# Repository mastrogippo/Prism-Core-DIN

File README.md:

## Prism Core boards and accessories

[Writeup and pics here](https://www.mastrogippo.it/2019/09/prism-core-boards/)

cover_pcb: Cover board layout

hv_in3: Base high voltage board for Prism Core

lato1: Left board with relay and HV detection for Prism Core

latoLV: Low voltage side board for Prism Core

top: Tob board with SKW92 module for Prism Core

top_hk2: Top board with HiLink module and RTC for Prism Core

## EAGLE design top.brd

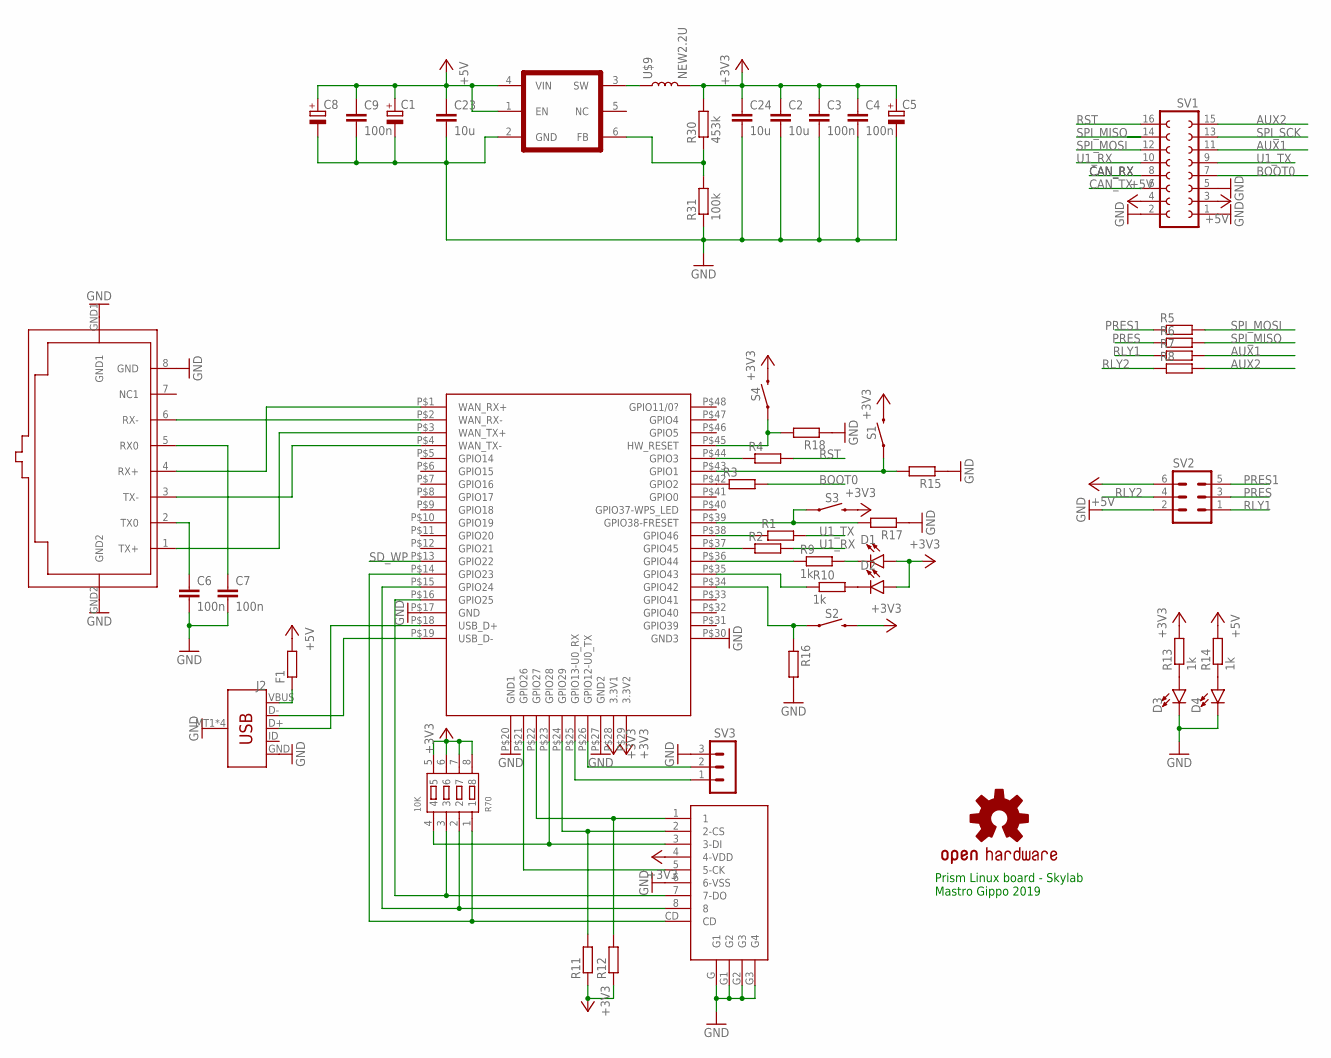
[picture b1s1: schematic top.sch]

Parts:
C1, C5, C8: CPOL-EUB/3528-21R; B/3528-21R
C2, C23, C24: 10u; C0805K
C3, C4, C6, C7, C9: 100n; C0805K
D1, D2: LED3MM; LED_3MM
D3, D4: LED1206; LED-1206
F1: R-EU_R0603; R0603
J2: USB_MICRO-B_SMT; USB-MICROB
R1, R2, R3, R4, R5, R6, R7, R8, R11, R12, R15, R16, R17, R18: R-EU_R0805; R0805
R9, R10, R13, R14: 1k; R0805
R30: 453k; R0805
R31: 100k; R0805
R70: 10K; RA1206-8
S1, S2, S4: MOMENTARY-SWITCH-SPST-SMD-6.0X3.5MM; TACTILE_SWITCH_SMD_6.0X3.5MM
S3: MOMENTARY-SWITCH-SPST-PTH-RIGHT-ANGLE; TACTILE_SWITCH_PTH_RIGHT_ANGLE
SV1: FE08-2
SV2: MA03-2
SV3: MA03-1
U$1: RJ45-TRAFO
U$2: SKW92B; SKW92
U$3: MICRO_SD; MICRO_SD_C
U$4: OSHW-LOGOS; OSHW-LOGO-S
U$8: TLV62658; SOT23-6
U$9: NEW2.2U; INDUCTOR_4X4MM

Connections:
+3V3: C2.1, C3.1, C4.1, C5.+, C24.1, D1.A, D2.A, R11.1, R12.1, R13.2, R30.2, R70.5, R70.6, R70.7, R70.8, S1.2, S2.2, S3.2, S4.2, U$2.P$28 (3.3V1), U$2.P$29 (3.3V2), U$3.4 (4-VDD), U$9.P$2 (2)
+5V: C1.+, C8.+, C9.1, C23.1, F1.2, R14.2, SV1.3, SV1.4, SV2.6, U$8.1 (EN), U$8.4 (VIN)
AUX1: R7.2, SV1.11
AUX2: R8.2, SV1.15
BOOT0: R3.2, SV1.7
CAN_RX: SV1.8
CAN_TX: SV1.6
GND: C1.-, C2.2, C3.2, C4.2, C5.-, C6.2, C7.2, C8.-, C9.2, C23.2, C24.2, D3.C, D4.C, J2.GND, J2.MT1 (SHIELD), J2.MT2 (SHIELD), J2.P$1 (SHIELD), J2.P$2 (SHIELD), R15.1, R16.2, R17.1, R18.1, R31.1, SV1.1, SV1.2, SV1.5, SV2.2, SV3.3, U$1.8 (GND), U$1.GND1, U$1.GND2, U$2.P$17 (GND), U$2.P$20 (GND1), U$2.P$27 (GND2), U$2.P$30 (GND3), U$3.6 (6-VSS), U$3.G (G1), U$3.G1 (G2), U$3.G2 (G3), U$3.G3 (G4), U$8.2 (GND)
unnamed: U$1.6 (RX-), U$2.P$2 (WAN_RX-)
unnamed: U$1.4 (RX+), U$2.P$1 (WAN_RX+)
unnamed: U$1.1 (TX+), U$2.P$3 (WAN_TX+)
unnamed: U$1.3 (TX-), U$2.P$4 (WAN_TX-)
unnamed: R11.2, U$2.P$24 (GPIO29), U$3.2 (2-CS)
unnamed: R70.4, U$2.P$23 (GPIO28), U$3.3 (3-DI)
unnamed: R12.2, U$2.P$22 (GPIO27), U$3.1
unnamed: U$2.P$21 (GPIO26), U$3.5 (5-CK)
unnamed: R70.3, U$2.P$16 (GPIO25), U$3.7 (7-DO)
unnamed: R70.2, U$2.P$15 (GPIO24), U$3.8
unnamed: R70.1, U$2.P$14 (GPIO23), U$3.CD
unnamed: R1.1, U$2.P$38 (GPIO46)
unnamed: R2.1, U$2.P$37 (GPIO45)
unnamed: R3.1, U$2.P$42 (GPIO2)
unnamed: R4.1, U$2.P$44 (GPIO3)
unnamed: D1.K (C), R9.2
unnamed: SV3.2, U$2.P$26 (GPIO12-U0_TX)
unnamed: SV3.1, U$2.P$25 (GPIO13-U0_RX)
unnamed: D2.K (C), R10.2
unnamed: R9.1, U$2.P$36 (GPIO44)
unnamed: R10.1, U$2.P$35 (GPIO43)
unnamed: D3.A, R13.1
unnamed: D4.A, R14.1
unnamed: R15.2, S1.1, U$2.P$43 (GPIO1)
unnamed: R16.1, S2.1, U$2.P$34 (GPIO42)
unnamed: R17.2, S3.1, U$2.P$39 (GPIO38-FRESET)
unnamed: R18.2, S4.1, U$2.P$45 (HW_RESET)
unnamed: C7.1, U$1.5 (RX0)
unnamed: C6.1, U$1.2 (TX0)
unnamed: J2.D+, U$2.P$18 (USB_D+)
unnamed: J2.D-, U$2.P$19 (USB_D-)
unnamed: F1.1, J2.VBUS
unnamed: U$8.3 (SW), U$9.P$1 (1)
unnamed: R30.1, R31.2, U$8.6 (FB)
PRES: R6.1, SV2.3
PRES1: R5.1, SV2.5
RLY1: R7.1, SV2.1
RLY2: R8.1, SV2.4
RST: R4.2, SV1.16
SD_WP: U$2.P$13 (GPIO22)
SPI_MISO: R6.2, SV1.14
SPI_MOSI: R5.2, SV1.12
SPI_SCK: SV1.13
U1_RX: R2.2, SV1.10
U1_TX: R1.2, SV1.9

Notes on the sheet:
Prism Linux board - Skylab Mastro Gippo 2019

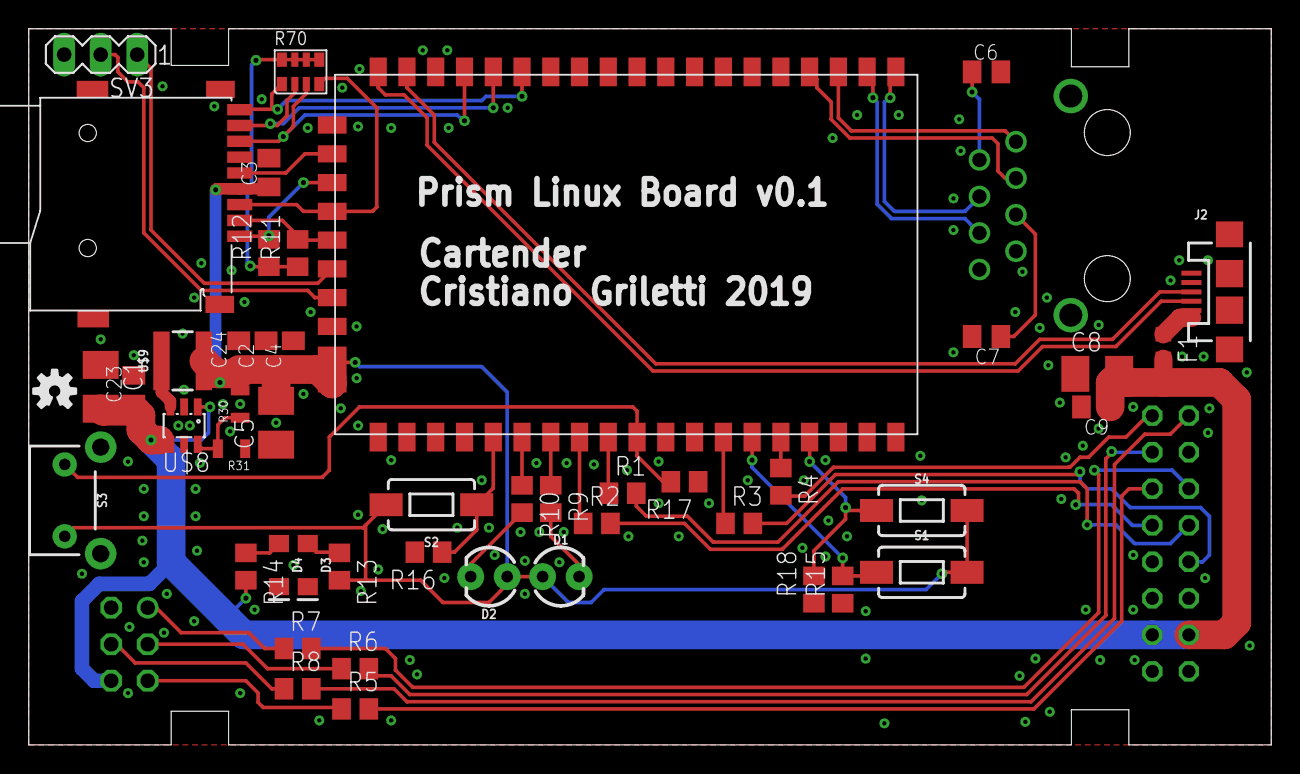
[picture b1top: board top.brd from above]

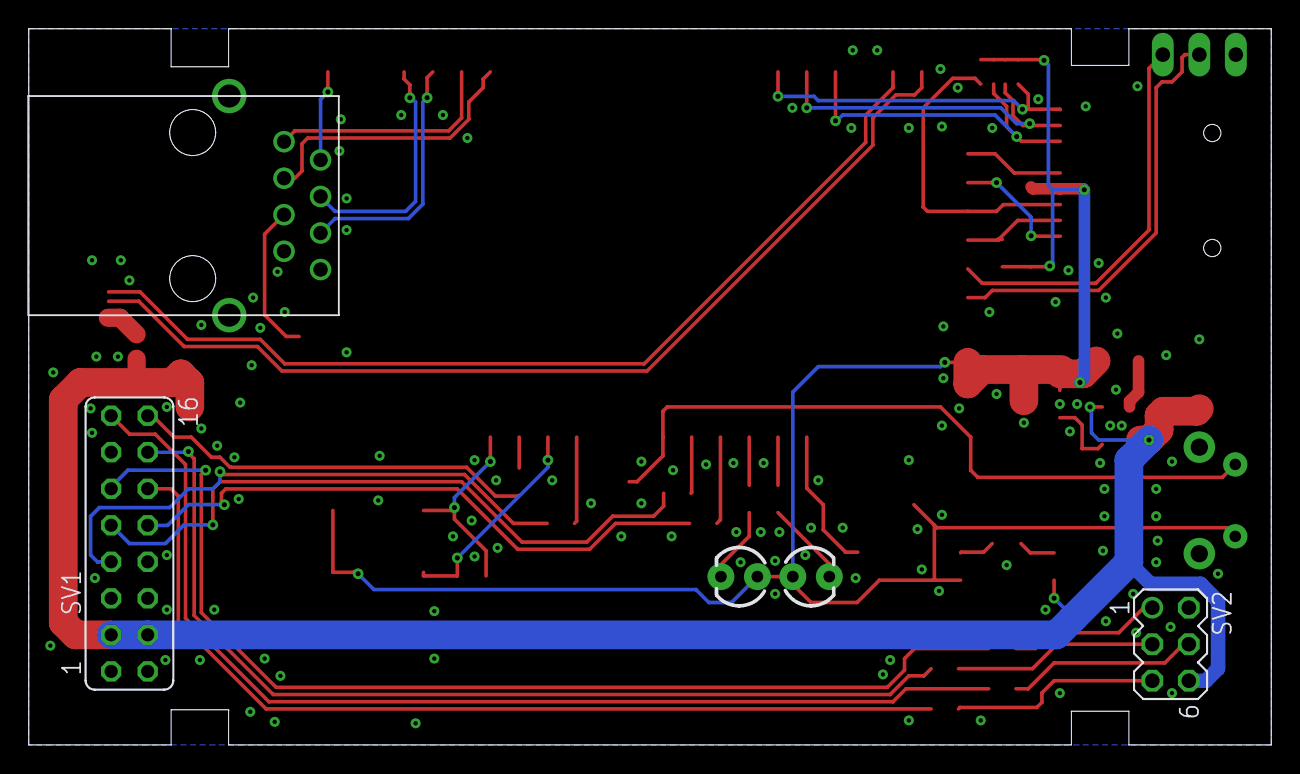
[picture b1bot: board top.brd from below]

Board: 2 copper layers, 86.4 x 49.8 mm, 51 parts (3 on the bottom side), 49 nets.

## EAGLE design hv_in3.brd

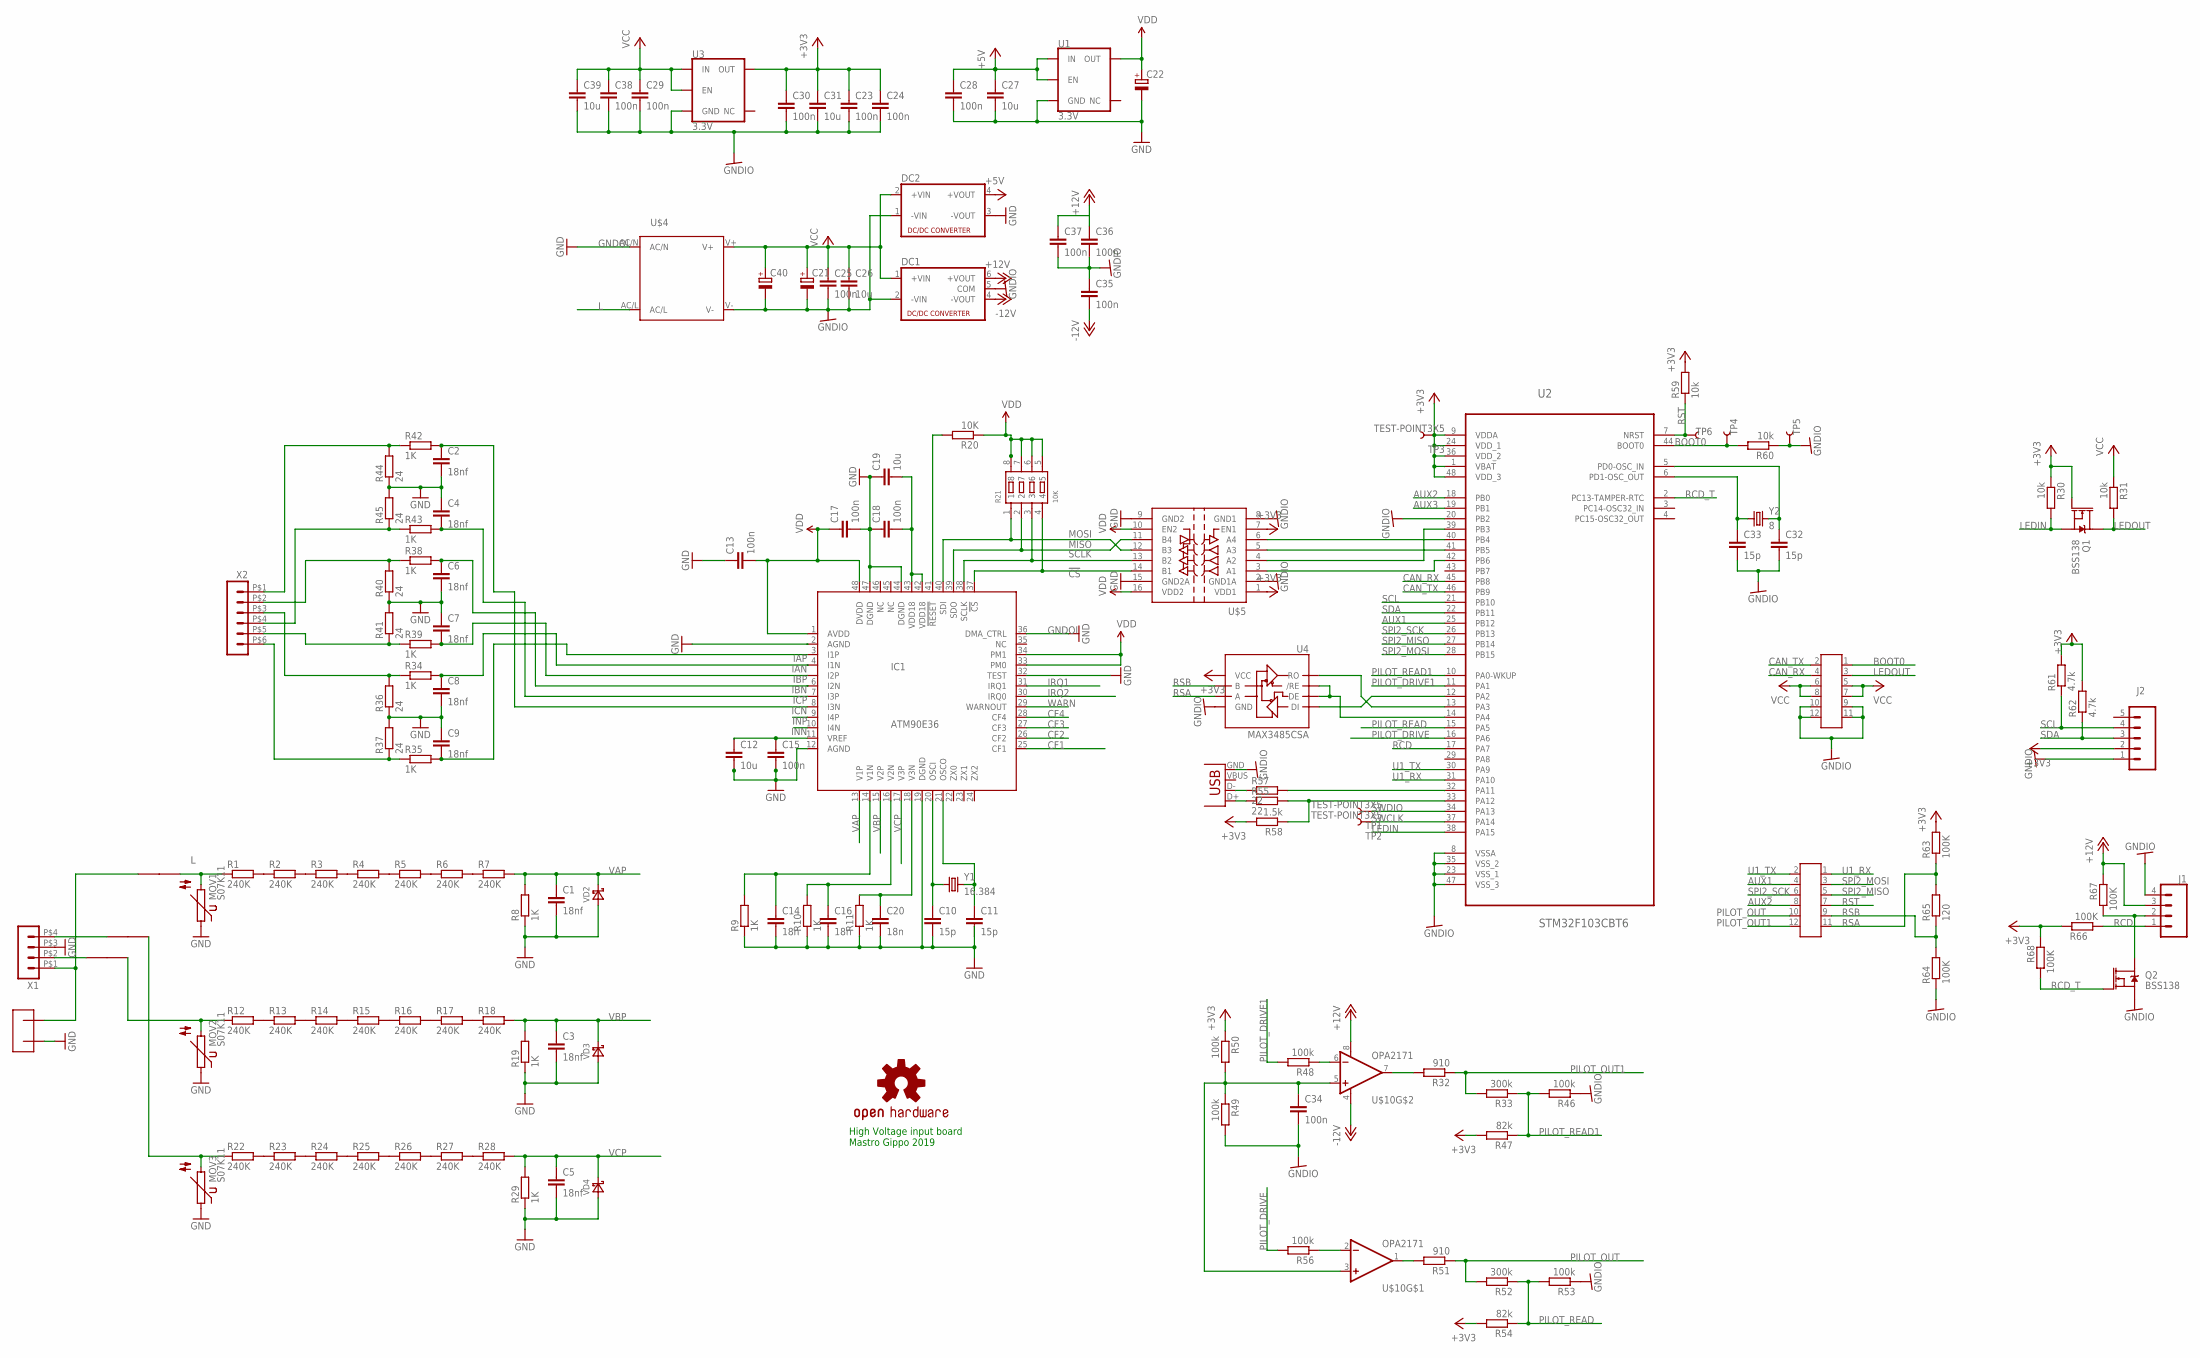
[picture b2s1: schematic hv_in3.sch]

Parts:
C1, C2, C3, C4, C5, C6, C7, C8, C9: 18nf; C0805K
C10, C11, C32, C33: 15p; C0805K
C12, C19, C26, C27, C31, C39: 10u; C0805K
C13, C15, C17, C18, C23, C24, C25, C28, C29, C30, C34, C35, C36, C37, C38: 100n; C0805K
C14, C16, C20: 18n; C0805K
C21, C22: CPOL-EU153CLV-0505; 153CLV-0505
C40: CPOL-EUB/3528-21R; B/3528-21R
DC1: NMA
DC2: NME
IC1: ATM90E36; TQFP48
J1: CONN_04SMD2; 1X04_1MM_RA
J2: CONN_05SMD2; 1X05_1MM_RA
MOV1, MOV2, MOV3: S07K11
Q1, Q2: BSS138; SOT23-3
R1, R2, R3, R4, R5, R6, R7, R12, R13, R14, R15, R16, R17, R18, R22, R23, R24, R25, R26, R27, R28: 240K; R0805
R8, R9, R10, R11, R19, R29, R34, R35, R38, R39, R42, R43: 1K; R0805
R20: 10K; R0805
R21: 10K; RA1206-8
R30, R31, R59, R60: 10k; R0805
R32, R51: 910; R1206
R33, R52: 300k; R0805
R36, R37, R40, R41, R44, R45: 24; R0805
R46, R48, R49, R50, R53, R56: 100k; R0805
R47, R54: 82k; R0805
R55, R57: 22; R0805
R58: 1.5k; R0805
R61, R62: 4.7k; R0805
R63, R64, R66, R67, R68: 100K; R0805
R65: 120; R0805
TP1, TP2, TP3, TP4, TP5, TP6: TEST-POINT3X5; PAD.03X.05
U1, U3: 3.3V; SOT23-5
U2: STM32F103CBT6; QFP50P900X900X160-48N
U4: MAX3485CSA; SO08
U$1, U$2, U$3: FUSE_2410; 2410_F
U$4: IRM_15/20IRM_15/20; IRM_15/20
U$5: SI8441IS1; SO16
U$6: ISOLATED_2P; STRIP_NOMIDDLE
U$7, U$8: CLP-106-02-F-D-P; CLP-106-02-X-D
U$9: OSHW-LOGOS; OSHW-LOGO-S
U$10: OPA2171; SO08
VD2, VD3, VD4: DIODE-SCHOTTKY-SOD523; SOD523
X1: HEADER_POS4_43045-0401; 43045-0400
X2: HEADER_POS6_43045-0600; 43045-0600
X3: USB-MICROB
Y1: 16.384; CRYSTAL-SMD-3.2X2.5MM
Y2: 8; CRYSTAL-SMD-3.2X2.5MM

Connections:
!CS: IC1.37 (!CS), R21.4, U$5.14 (B1)
+3V3: C23.1, C24.1, C30.1, C31.1, J2.2, Q1.1 (G), R30.1, R47.2, R50.1, R54.2, R58.2, R59.2, R61.2, R62.2, R63.2, R66.2, R68.2, TP3.P$1, U2.1 (VBAT), U2.9 (VDDA), U2.24 (VDD_1), U2.36 (VDD_2), U2.48 (VDD_3), U3.5 (OUT), U4.8 (VCC), U$5.1 (VDD1), U$5.7 (EN1)
+5V: C27.1, C28.1, DC2.4 (+VOUT), U1.1 (IN), U1.3 (EN)
+12V: C36.1, C37.1, DC1.6 (+VOUT), J1.3, R67.2, U$10.8 (V+)
-12V: C35.2, DC1.4 (-VOUT), U$10.4 (V-)
AUX1: U2.25 (PB12), U$7.4
AUX2: U2.18 (PB0), U$7.8
AUX3: U2.19 (PB1)
BOOT0: R60.2, TP4.P$1, U2.44 (BOOT0), U$8.1
CAN_RX: U2.45 (PB8), U$8.4
CAN_TX: U2.46 (PB9), U$8.2
CF1: IC1.25 (CF1)
CF2: IC1.26 (CF2)
CF3: IC1.27 (CF3)
CF4: IC1.28 (CF4)
GNDIO: C21.-, C23.2, C24.2, C25.2, C26.2, C29.2, C30.2, C31.2, C32.2, C33.2, C34.2, C35.1, C36.2, C37.2, C38.2, C39.2, C40.-, DC1.2 (-VIN), DC1.5 (COM), DC2.1 (-VIN), J1.4, J2.1, Q2.2 (S), R46.1, R49.2, R53.1, R60.1, R64.1, TP5.P$1, U2.8 (VSSA), U2.20 (PB2), U2.23 (VSS_1), U2.35 (VSS_2), U2.47 (VSS_3), U3.2 (GND), U4.5 (GND), U$4.V-, U$5.2 (GND1A), U$5.8 (GND1), U$8.9, U$8.10, U$8.11, U$8.12, X3.GND
GNDOI: C1.2, C2.2, C3.2, C4.1, C5.2, C6.2, C7.1, C8.2, C9.1, C10.2, C11.2, C12.2, C13.1, C14.2, C15.2, C16.2, C17.2, C18.1, C19.1, C20.2, C22.-, C27.2, C28.2, DC2.3 (-VOUT), IC1.2 (AGND), IC1.12 (AGND), IC1.19 (DGND), IC1.32 (TEST), IC1.36 (DMA_CTRL), IC1.44 (DGND), IC1.47 (DGND), MOV1.1, MOV2.1, MOV3.1, R8.1, R9.1, R10.1, R11.1, R19.1, R29.1, R36.1, R37.2, R40.1, R41.2, R44.1, R45.2, U1.2 (GND), U$4.AC/N, U$5.9 (GND2), U$5.15 (GND2A), U$6.P$2, VD2.A, VD3.A, VD4.A, X1.P$3 (3)
IAN: C8.1, IC1.4 (I1N), R34.2
IAP: C9.2, IC1.3 (I1P), R35.2
IBN: C6.1, IC1.6 (I2N), R38.2
IBP: C7.2, IC1.5 (I2P), R39.2
ICN: C2.1, IC1.8 (I3N), R42.2
ICP: C4.2, IC1.7 (I3P), R43.2
INN: IC1.10 (I4N)
INP: IC1.9 (I4P)
IRQ1: IC1.31 (IRQ1)
IRQ2: IC1.30 (IRQ0)
L: MOV1.2, R1.1, U$1.P$2, U$4.AC/L
LEDIN: Q1.2 (S), R30.2, U2.38 (PA15)
LEDOUT: Q1.3 (D), R31.2, U$8.3
MISO: IC1.39 (SDO), R21.2, U$5.11 (B4)
MOSI: IC1.40 (SDI), R21.1, U$5.12 (B3)
unnamed: U$3.P$2, X1.P$4 (4)
unnamed: R1.2, R2.1
unnamed: R2.2, R3.1
unnamed: R3.2, R4.1
unnamed: R4.2, R5.1
unnamed: R5.2, R6.1
unnamed: R6.2, R7.1
unnamed: U$2.P$2, X1.P$2 (2)
unnamed: MOV2.2, R12.1, U$2.P$1
unnamed: C32.1, U2.5 (PD0-OSC_IN), Y2.3 (2)
unnamed: C33.1, U2.6 (PD1-OSC_OUT), Y2.1
unnamed: U$1.P$1, U$6.P$1, X1.P$1 (1)
unnamed: U2.40 (PB4), U$5.6 (A4)
unnamed: U2.41 (PB5), U$5.5 (A3)
unnamed: R12.2, R13.1
unnamed: R13.2, R14.1
unnamed: R14.2, R15.1
unnamed: R15.2, R16.1
unnamed: R16.2, R17.1
unnamed: R17.2, R18.1
unnamed: C14.1, IC1.14 (V1N), R9.2
unnamed: C16.1, IC1.16 (V2N), R10.2
unnamed: U2.39 (PB3), U$5.4 (A2)
unnamed: C20.1, IC1.18 (V3N), R11.2
unnamed: MOV3.2, R22.1, U$3.P$1
unnamed: R22.2, R23.1
unnamed: R23.2, R24.1
unnamed: R24.2, R25.1
unnamed: R25.2, R26.1
unnamed: R26.2, R27.1
unnamed: R27.2, R28.1
unnamed: C18.2, C19.2, IC1.42 (VDD18), IC1.43 (VDD18)
unnamed: C10.1, IC1.20 (OSCI), Y1.1
unnamed: C11.1, IC1.21 (OSCO), Y1.3 (2)
unnamed: R34.1, R36.2, X2.P$3 (3)
unnamed: R39.1, R41.1, X2.P$5 (5)
unnamed: U2.42 (PB6), U$5.3 (A1)
unnamed: R55.1, X3.D+
unnamed: R57.1, X3.D-
unnamed: R43.1, R45.1, X2.P$4 (4)
unnamed: R57.2, U2.32 (PA11)
unnamed: R35.1, R37.1, X2.P$6 (6)
unnamed: R42.1, R44.2, X2.P$1 (1)
unnamed: R55.2, R58.1, U2.33 (PA12)
unnamed: R51.2, U$10.1 (OUT)
unnamed: R56.1, U$10.2 (-IN)
unnamed: R38.1, R40.2, X2.P$2 (2)
unnamed: R48.1, U$10.6 (-IN)
unnamed: C34.1, R49.1, R50.2, U$10.3 (+IN), U$10.5 (+IN)
unnamed: R32.2, U$10.7 (OUT)
unnamed: U2.12 (PA2), U4.4 (DI)
unnamed: U2.13 (PA3), U4.1 (RO)
unnamed: C12.1, C15.1, IC1.11 (VREF)
unnamed: U2.14 (PA4), U4.2 (/RE), U4.3 (DE)
unnamed: J1.2, Q2.3 (D), R67.1
PILOT_DRIVE: R56.2, U2.16 (PA6)
PILOT_DRIVE1: R48.2, U2.11 (PA1)
PILOT_OUT: R51.1, R52.2, U$7.10
PILOT_OUT1: R32.1, R33.2, U$7.12
PILOT_READ: R52.1, R53.2, R54.1, U2.15 (PA5)
PILOT_READ1: R33.1, R46.2, R47.1, U2.10 (PA0-WKUP)
RCD: J1.1, R66.1, U2.17 (PA7)
RCD_T: Q2.1 (G), R68.1, U2.2 (PC13-TAMPER-RTC)
RES: IC1.41 (!RESET), R20.2
RSA: R63.1, R65.2, U4.6 (A), U$7.11
RSB: R64.2, R65.1, U4.7 (B), U$7.9
RST: R59.1, TP6.P$1, U2.7 (NRST), U$7.7
SCL: J2.4, R61.1, U2.21 (PB10)
SCLK: IC1.38 (SCLK), R21.3, U$5.13 (B2)
SDA: J2.3, R62.1, U2.22 (PB11)
SPI2_MISO: U2.27 (PB14), U$7.5
SPI2_MOSI: U2.28 (PB15), U$7.3
SPI2_SCK: U2.26 (PB13), U$7.6
SWCLK: TP2.P$1, U2.37 (PA14)
SWDIO: TP1.P$1, U2.34 (PA13)
U1_RX: U2.31 (PA10), U$7.1
U1_TX: U2.30 (PA9), U$7.2
VAP: C1.1, IC1.13 (V1P), R7.2, R8.2, VD2.C
VBP: C3.1, IC1.15 (V2P), R18.2, R19.2, VD3.C
VCC: C21.+, C25.1, C26.1, C29.1, C38.1, C39.1, C40.+, DC1.1 (+VIN), DC2.2 (+VIN), R31.1, U3.1 (IN), U3.3 (EN), U$4.V+, U$8.5, U$8.6, U$8.7, U$8.8
VCP: C5.1, IC1.17 (V3P), R28.2, R29.2, VD4.C
VDD: C13.2, C17.1, C22.+, IC1.1 (AVDD), IC1.33 (PM0), IC1.34 (PM1), IC1.48 (DVDD), R20.1, R21.5, R21.6, R21.7, R21.8, U1.5 (OUT), U$5.10 (EN2), U$5.16 (VDD2)
WARN: IC1.29 (WARNOUT)

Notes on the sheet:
High Voltage input board Mastro Gippo 2019

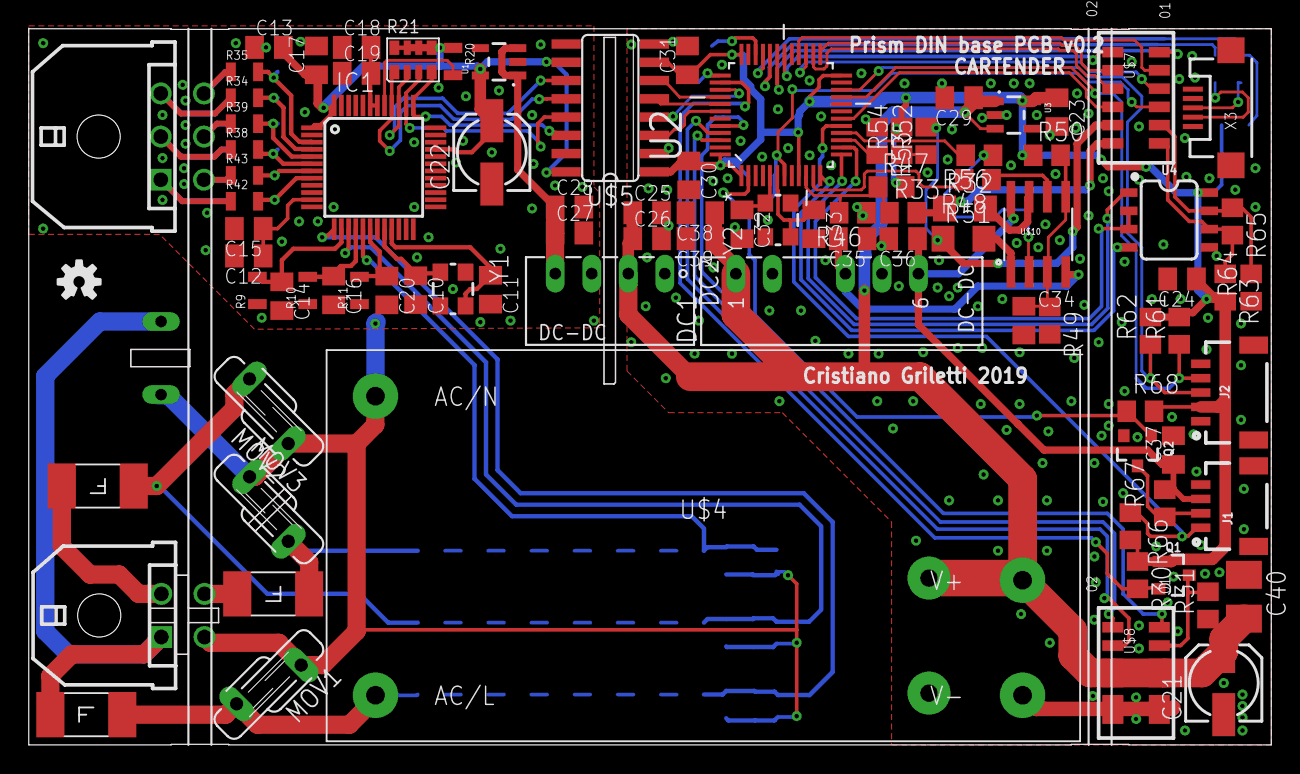
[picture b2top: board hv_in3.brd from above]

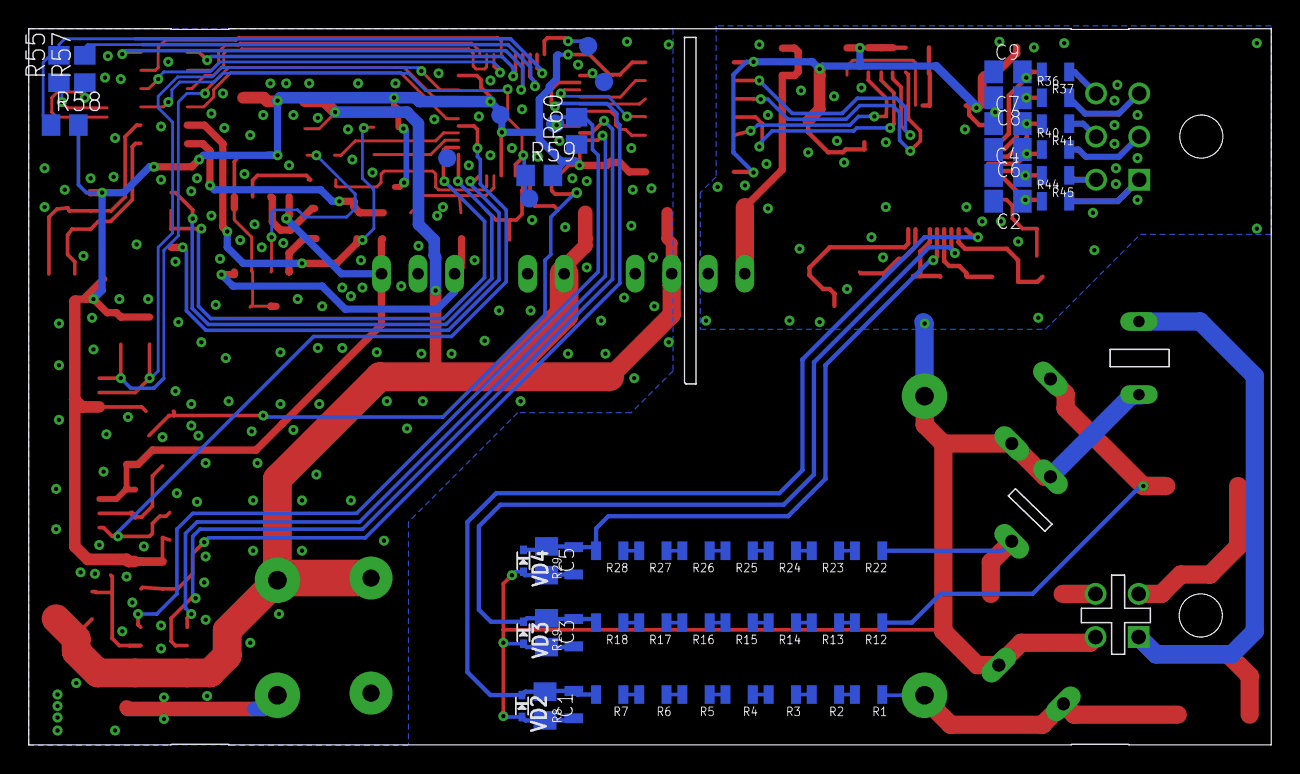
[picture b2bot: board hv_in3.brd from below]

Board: 2 copper layers, 86.3 x 49.7 mm, 146 parts (53 on the bottom side), 105 nets.

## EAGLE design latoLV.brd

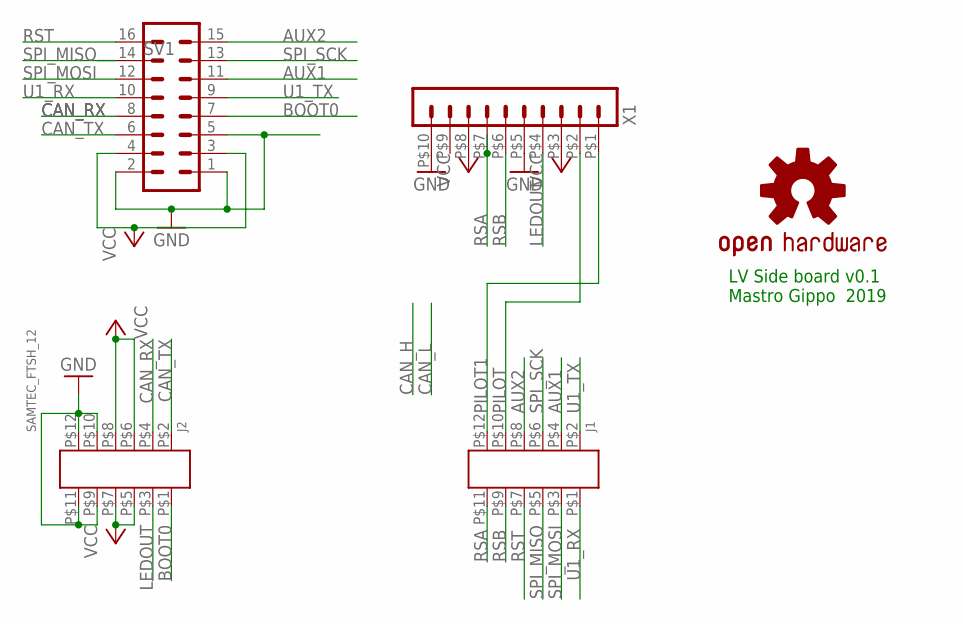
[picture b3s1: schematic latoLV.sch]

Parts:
J1, J2: SAMTEC_FTSH_12; 6X2_1MM
SV1: MA08-2
U$1: OSHW-LOGOS; OSHW-LOGO-S
X1: HEADER_POS10_43045-1012; 43045-1012

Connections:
AUX1: J1.P$4, SV1.11
AUX2: J1.P$8, SV1.15
BOOT0: J2.P$1, SV1.7
CAN_RX: J2.P$4, SV1.8
CAN_TX: J2.P$2, SV1.6
GND: J2.P$9, J2.P$10, J2.P$11, J2.P$12, SV1.1, SV1.2, SV1.5, X1.P$5 (5), X1.P$10 (10)
LEDOUT: J2.P$3, X1.P$4 (4)
PILOT: J1.P$10, X1.P$2 (2)
PILOT1: J1.P$12, X1.P$1 (1)
RSA: J1.P$11, X1.P$7 (7)
RSB: J1.P$9, X1.P$6 (6)
RST: J1.P$7, SV1.16
SPI_MISO: J1.P$5, SV1.14
SPI_MOSI: J1.P$3, SV1.12
SPI_SCK: J1.P$6, SV1.13
U1_RX: J1.P$1, SV1.10
U1_TX: J1.P$2, SV1.9
VCC: J2.P$5, J2.P$6, J2.P$7, J2.P$8, SV1.3, SV1.4, X1.P$3 (3), X1.P$8 (8)

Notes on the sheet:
LV Side board v0.1 Mastro Gippo 2019

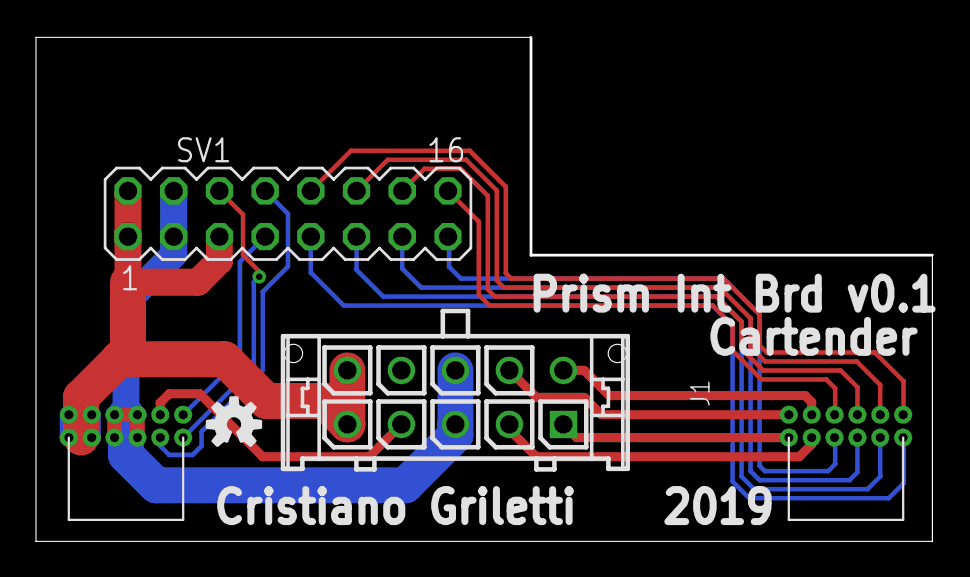
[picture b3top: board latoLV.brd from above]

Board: 2 copper layers, 49.7 x 27.9 mm, 5 parts (0 on the bottom side), 18 nets.

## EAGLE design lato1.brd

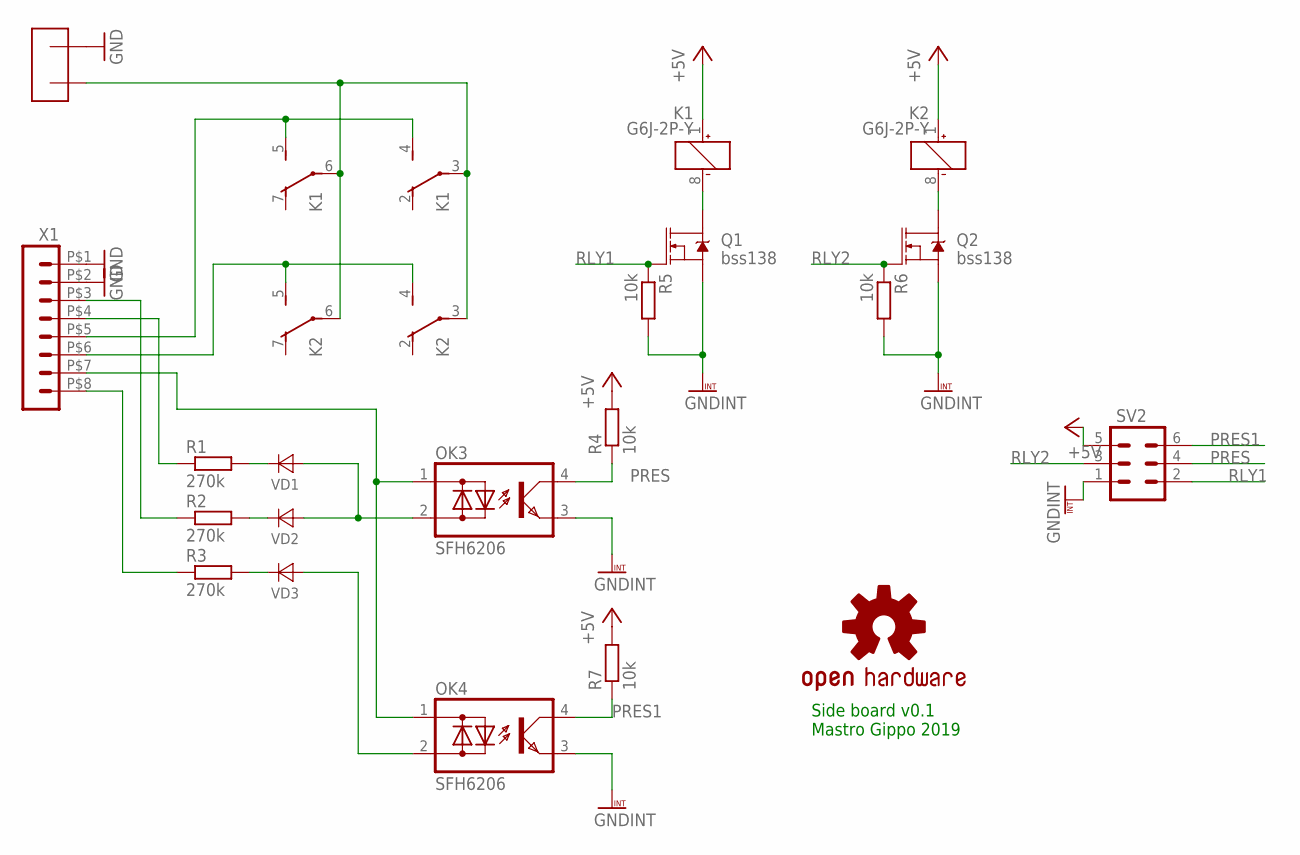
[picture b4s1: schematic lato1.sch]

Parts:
K1, K2: G6J-2P-Y
OK3, OK4: SFH6206; DIL4-SMD
Q1, Q2: bss138; SOT23-3
R1, R2, R3: 270k; R1210
R4, R5, R6, R7: 10k; R0805
SV2: MA03-2
U$1: ISOLATED_2P; STRIP_NOMIDDLE
U$2: OSHW-LOGOS; OSHW-LOGO-S
VD1, VD2, VD3: DIODE-STANDARD-SOD323; SOD323
X1: HEADER_POS8_43045-0812; 43045-0812

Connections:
+5V: K1.1 (+), K2.1 (+), R4.2, R7.2, SV2.5
GND: U$1.P$1, X1.P$1 (1), X1.P$2 (2)
GNDINT: OK3.3 (E), OK4.3 (E), Q1.2 (S), Q2.2 (S), R5.2, R6.2, SV2.1
unnamed: K1.3, K1.6, K2.3, K2.6, U$1.P$2
unnamed: K1.4 (S), K1.5 (S), X1.P$5 (5)
unnamed: K2.4 (S), K2.5 (S), X1.P$6 (6)
unnamed: R1.1, X1.P$4 (4)
unnamed: R2.1, X1.P$3 (3)
unnamed: R3.1, X1.P$8 (8)
unnamed: OK3.1 (AC1), OK4.1 (AC1), X1.P$7 (7)
unnamed: R1.2, VD1.C
unnamed: R3.2, VD3.C
unnamed: OK4.2 (AC2), VD3.A
unnamed: K1.8 (-), Q1.3 (D)
unnamed: R2.2, VD2.C
unnamed: K2.8 (-), Q2.3 (D)
unnamed: OK3.2 (AC2), VD1.A, VD2.A
PRES: OK3.4 (C), R4.1, SV2.4
PRES1: OK4.4 (C), R7.1, SV2.6
RLY1: Q1.1 (G), R5.1, SV2.2
RLY2: Q2.1 (G), R6.1, SV2.3

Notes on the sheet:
Side board v0.1 Mastro Gippo 2019

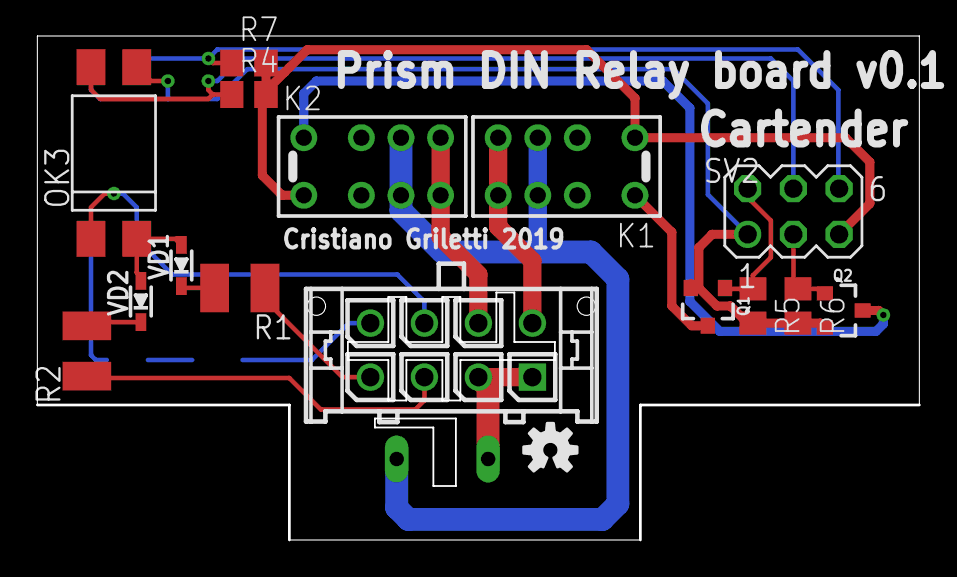
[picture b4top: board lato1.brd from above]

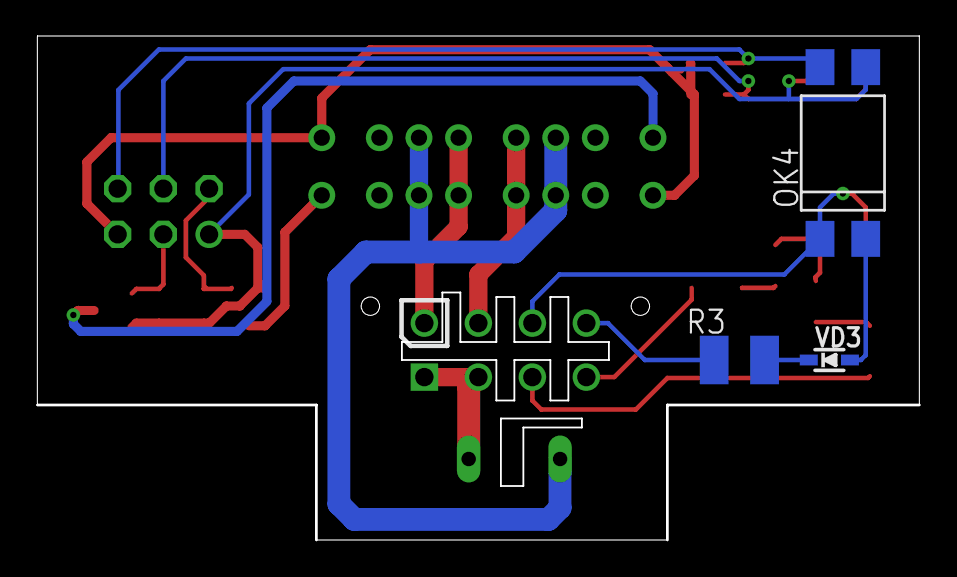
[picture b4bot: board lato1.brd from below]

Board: 2 copper layers, 49.0 x 27.9 mm, 20 parts (3 on the bottom side), 21 nets.

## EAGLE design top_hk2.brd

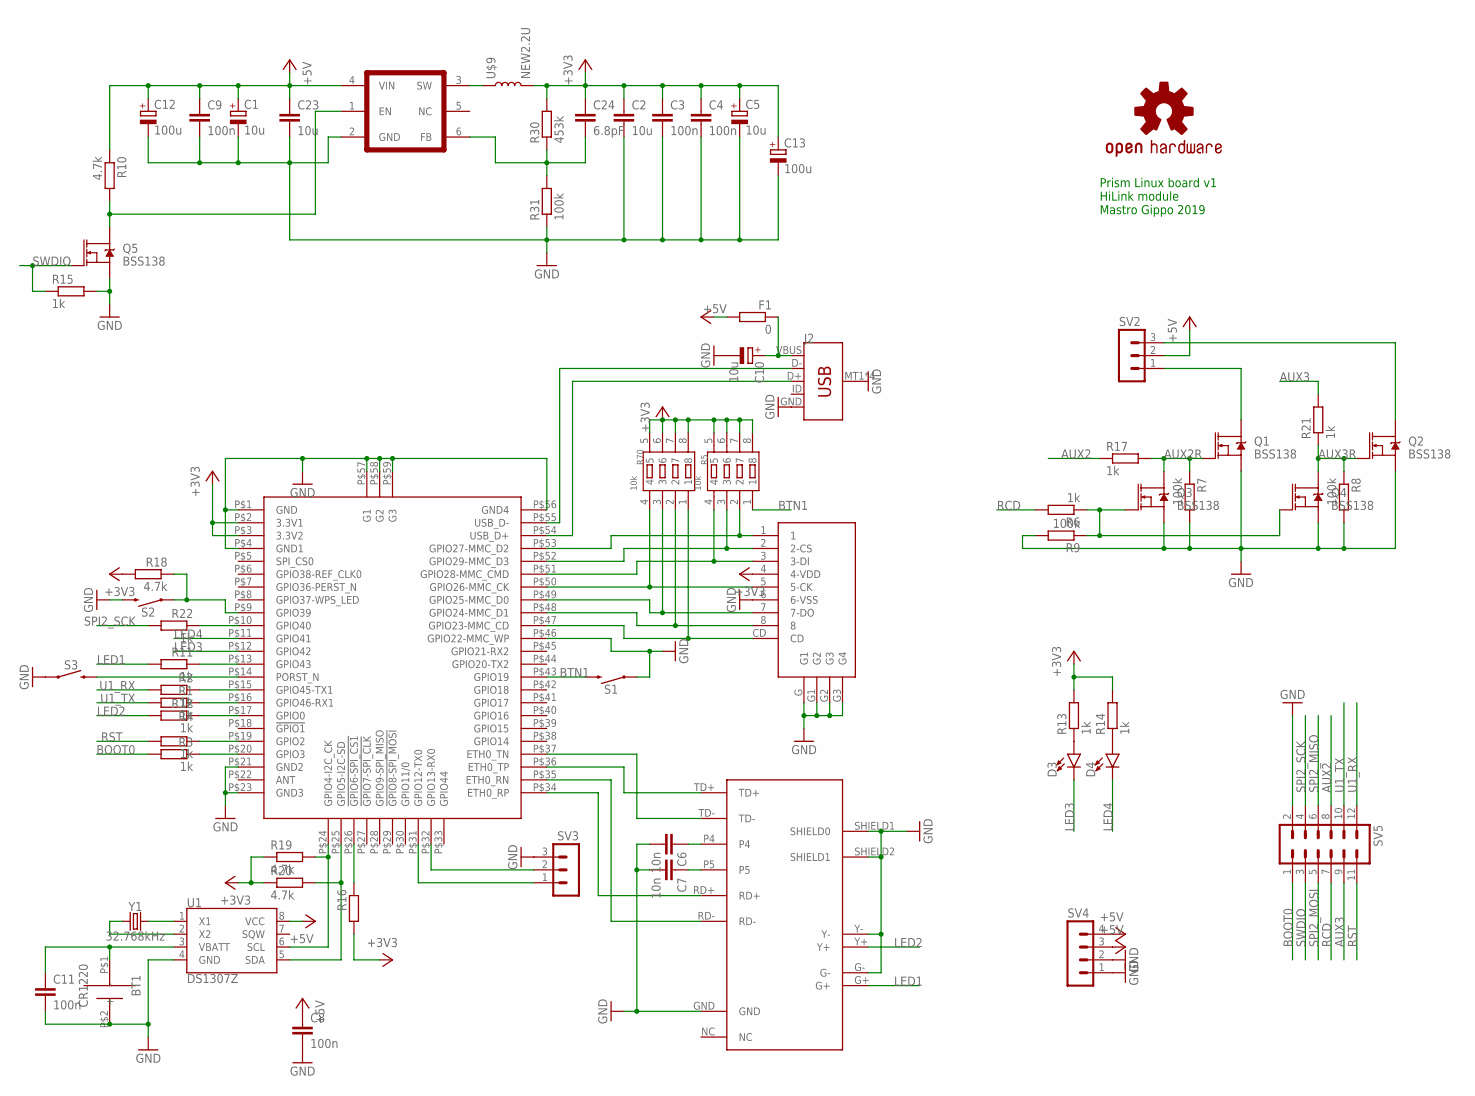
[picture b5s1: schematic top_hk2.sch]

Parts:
BT1: CR1220
C1, C5, C10: 10u; B/3528-21R
C2, C23: 10u; C0805K
C3, C4, C8, C9, C11: 100n; C0805K
C6, C7: 10n; C0805K
C12, C13: 100u; 153CLV-0505
C24: 6.8pF; C0805K
D3, D4: LED1206; LED-1206
F1: 0; R0603
J2: USB_MICRO-B_SMT; USB-MICROB
Q1, Q2, Q3, Q4, Q5: BSS138; SOT23-3
R1, R2, R3, R4, R6, R11, R12, R13, R14, R15, R17, R21, R22: 1k; R0805
R5, R70: 10k; RA1206-8
R7, R8, R9, R31: 100k; R0805
R10, R18, R19, R20: 4.7k; R0805
R16: R-EU_R0805; R0805
R30: 453k; R0805
S1, S2: MOMENTARY-SWITCH-SPST-SMD-6.0X3.5MM; TACTILE_SWITCH_SMD_6.0X3.5MM
S3: MOMENTARY-SWITCH-SPST-PTH-RIGHT-ANGLE; TACTILE_SWITCH_PTH_RIGHT_ANGLE
SV2, SV3: MA03-1
SV4: MA04-1
SV5: MA06-2
U1: DS1307Z; SO08-0.15
U$1: OSHW-LOGOS; OSHW-LOGO-S
U$2: HLK-7688A
U$3: MICRO_SD; MICRO_SD_C
U$4: HR911105A; RJ45
U$8: TLV62658; SOT23-6
U$9: NEW2.2U; INDUCTOR_4X4MM
Y1: 32.768kHz; CRYSTAL-SMD-2X6-CYL

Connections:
+3V3: C2.1, C3.1, C4.1, C5.+, C13.+, C24.1, R5.5, R5.6, R5.7, R5.8, R13.2, R14.2, R16.2, R18.2, R19.1, R20.1, R30.2, R70.5, R70.6, R70.7, R70.8, U$2.P$2 (3.3V1), U$2.P$3 (3.3V2), U$3.4 (4-VDD), U$9.P$2 (2)
+5V: C1.+, C8.1, C9.1, C12.+, C23.1, F1.2, R10.1, SV2.2, SV4.3, SV4.4, U1.8 (VCC), U$8.4 (VIN)
AUX2: R17.1, SV5.8
AUX2R: Q1.1 (G), Q3.3 (D), R7.1, R17.2
AUX3: R21.2, SV5.9
AUX3R: Q2.1 (G), Q4.3 (D), R8.1, R21.1
BOOT0: R3.2, SV5.1
BTN1: R5.1, S1.2, U$2.P$43 (GPIO19)
GND: BT1.P$2 (-), C1.-, C2.2, C3.2, C4.2, C5.-, C6.2, C7.2, C8.2, C9.2, C10.-, C11.2, C12.-, C13.-, C23.2, J2.GND, J2.MT1 (SHIELD), J2.MT2 (SHIELD), J2.P$1 (SHIELD), J2.P$2 (SHIELD), Q1.2 (S), Q2.2 (S), Q3.2 (S), Q4.2 (S), Q5.2 (S), R7.2, R8.2, R9.2, R15.2, R31.1, S1.1, S2.2, S3.1, SV3.3, SV4.1, SV4.2, SV5.2, U1.4 (GND), U$2.P$1 (GND), U$2.P$4 (GND1), U$2.P$21 (GND2), U$2.P$23 (GND3), U$2.P$46 (GPIO22-MMC_WP), U$2.P$56 (GND4), U$2.P$57 (G1), U$2.P$58 (G2), U$2.P$59 (G3), U$3.6 (6-VSS), U$3.G (G1), U$3.G1 (G2), U$3.G2 (G3), U$3.G3 (G4), U$4.G-, U$4.GND, U$4.SHIELD1 (SHIELD0), U$4.SHIELD2 (SHIELD1), U$4.Y-, U$8.2 (GND)
LED1: R11.2, U$4.G+
LED2: R12.2, U$4.Y+
LED3: D3.C, U$2.P$12 (GPIO42)
LED4: D4.C, U$2.P$11 (GPIO41)
unnamed: C6.1, U$4.P4
unnamed: C7.1, U$4.P5
unnamed: R2.1, U$2.P$15 (GPIO45-TX1)
unnamed: R1.1, U$2.P$16 (GPIO46-RX1)
unnamed: R5.3, U$2.P$52 (GPIO29-MMC_D3), U$3.2 (2-CS)
unnamed: R5.4, U$2.P$51 (GPIO28-MMC_CMD), U$3.3 (3-DI)
unnamed: R5.2, U$2.P$53 (GPIO27-MMC_D2), U$3.1
unnamed: R70.4, U$2.P$50 (GPIO26-MMC_CK), U$3.5 (5-CK)
unnamed: U$2.P$36 (ETH0_TP), U$4.TD+
unnamed: R19.2, U1.6 (SCL), U$2.P$24 (GPIO4-I2C_CK)
unnamed: R20.2, U1.5 (SDA), U$2.P$25 (GPIO5-I2C-SD)
unnamed: R4.1, U$2.P$19 (GPIO2)
unnamed: R3.1, U$2.P$20 (GPIO3)
unnamed: R70.2, U$2.P$48 (GPIO24-MMC_D1), U$3.8
unnamed: R11.1, U$2.P$13 (GPIO43)
unnamed: Q5.3 (D), R10.2, U$8.1 (EN)
unnamed: SV3.2, U$2.P$32 (GPIO13-RX0)
unnamed: SV3.1, U$2.P$31 (GPIO12-TX0)
unnamed: R16.1, U$2.P$26 (!GPIO6-SPI_CS1)
unnamed: R18.1, S2.1, U$2.P$9 (GPIO39)
unnamed: R22.1, U$2.P$10 (GPIO40)
unnamed: D3.A, R13.1
unnamed: D4.A, R14.1
unnamed: S3.2, U$2.P$14 (PORST_N)
unnamed: Q3.1 (G), Q4.1 (G), R6.1, R9.1
unnamed: J2.D+, U$2.P$54 (USB_D+)
unnamed: J2.D-, U$2.P$55 (USB_D-)
unnamed: C10.+, F1.1, J2.VBUS
unnamed: R70.1, U$2.P$47 (GPIO23-MMC_CD), U$3.CD
unnamed: R70.3, U$2.P$49 (GPIO25-MMC_D0), U$3.7 (7-DO)
unnamed: U1.2 (X2), Y1.X1 (1)
unnamed: U1.1 (X1), Y1.X2 (2)
unnamed: BT1.P$1 (+), C11.1, U1.3 (VBATT)
unnamed: Q1.3 (D), SV2.1
unnamed: U$2.P$37 (ETH0_TN), U$4.TD-
unnamed: U$2.P$35 (ETH0_RN), U$4.RD-
unnamed: U$8.3 (SW), U$9.P$1 (1)
unnamed: U$2.P$34 (ETH0_RP), U$4.RD+
unnamed: Q2.3 (D), SV2.3
unnamed: R12.1, U$2.P$17 (GPIO0)
unnamed: C24.2, R30.1, R31.2, U$8.6 (FB)
RCD: R6.2, SV5.7
RST: R4.2, SV5.11
SPI2_MISO: SV5.6
SPI2_MOSI: SV5.5
SPI2_SCK: R22.2, SV5.4
SWDIO: Q5.1 (G), R15.1, SV5.3
U1_RX: R2.2, SV5.12
U1_TX: R1.2, SV5.10

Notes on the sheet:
Prism Linux board v1 HiLink module Mastro Gippo 2019

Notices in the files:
parts and their libraries:
SparkFun: Licensing: CC v3.0 Share-Alike You are welcome to use this library for commercial purposes.
SparkFun-IC-Power: Licensing: Creative Commons ShareAlike 4.0 International - https://creativecommons.org/licenses/by-sa/4.0
